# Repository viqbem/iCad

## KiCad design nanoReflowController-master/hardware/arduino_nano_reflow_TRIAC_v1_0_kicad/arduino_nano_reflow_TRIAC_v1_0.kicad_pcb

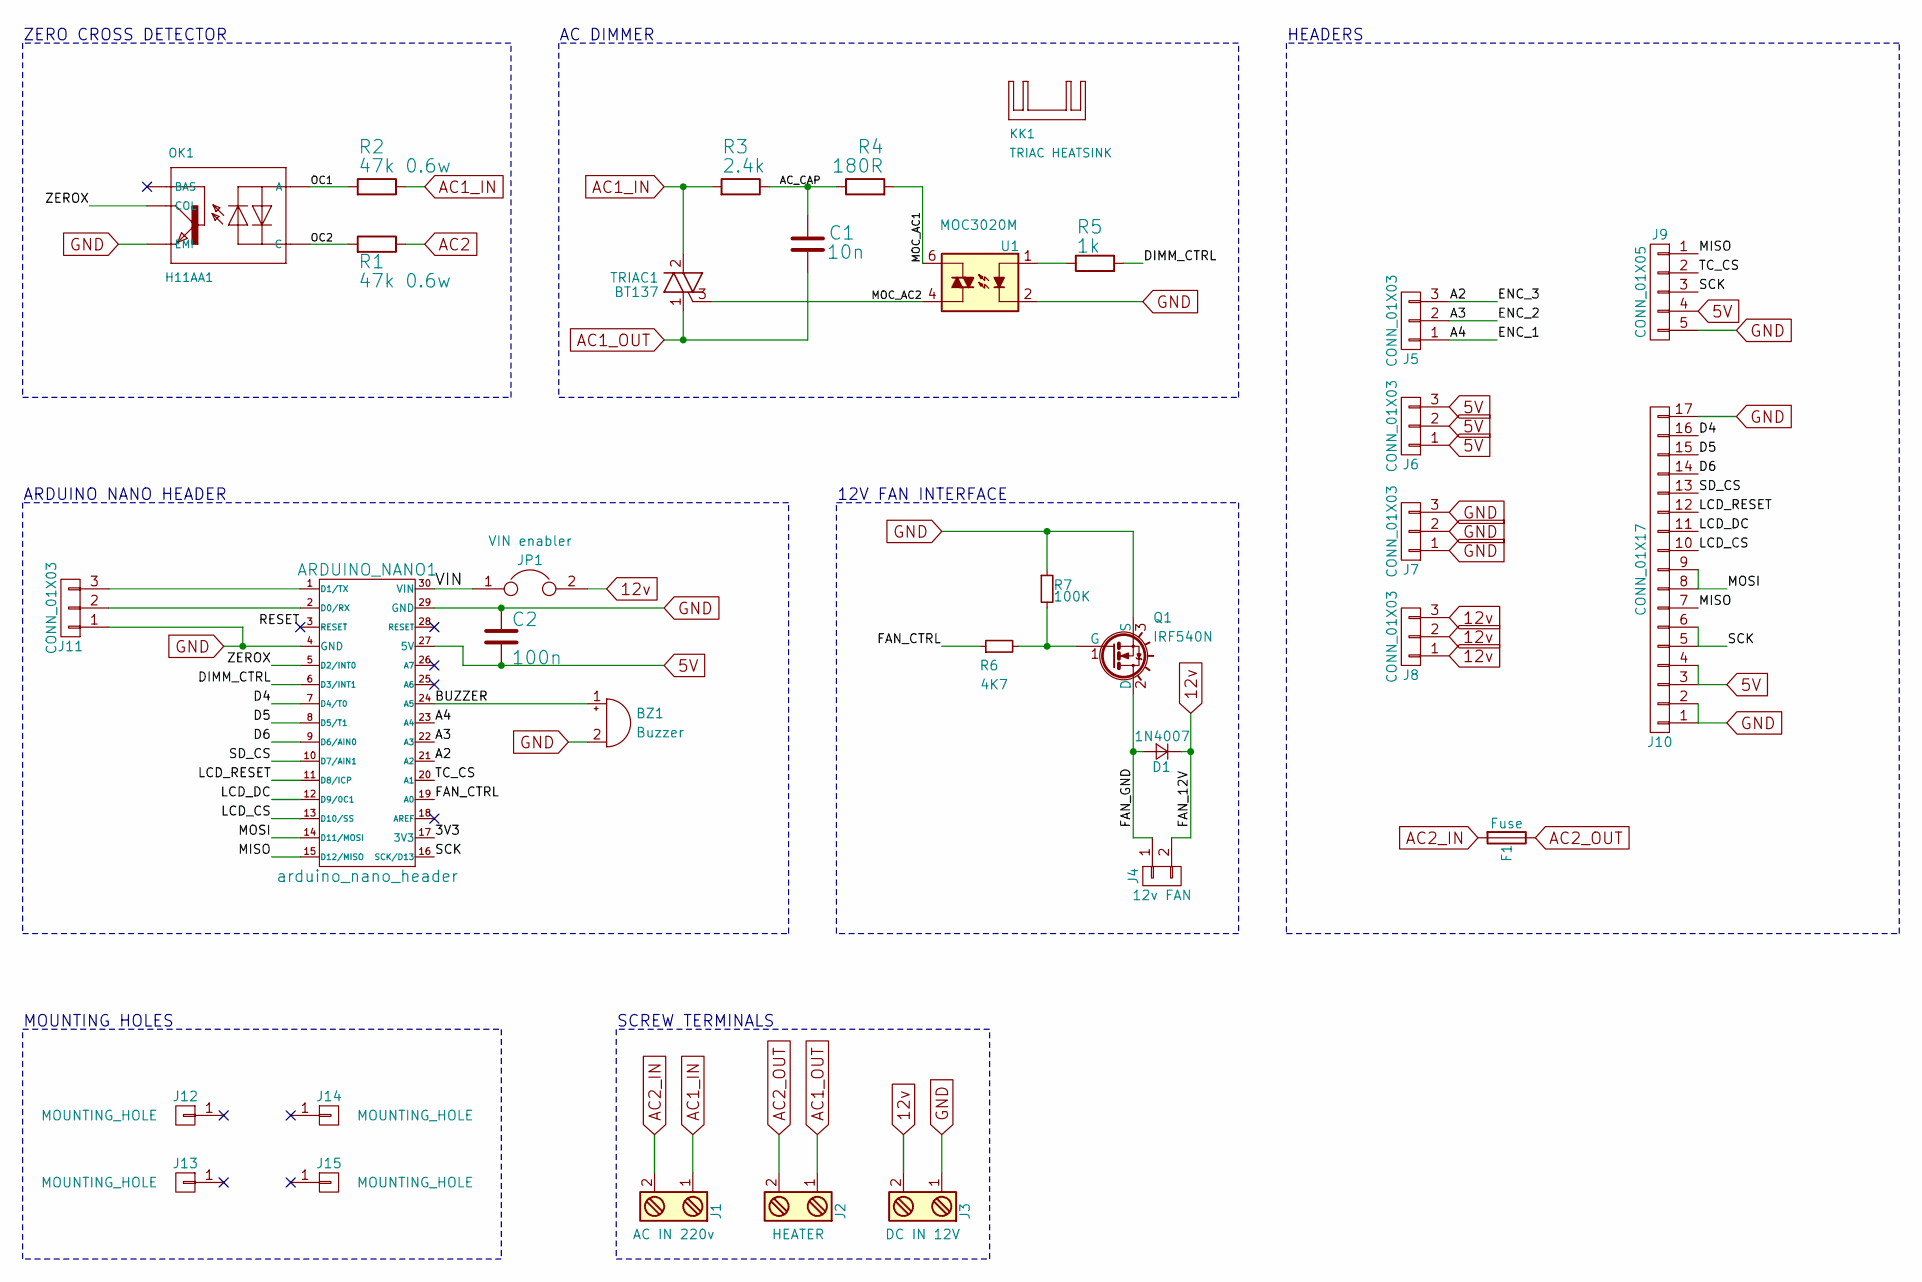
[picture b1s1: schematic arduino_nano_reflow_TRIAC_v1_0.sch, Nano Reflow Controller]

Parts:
ARDUINO_NANO1: arduino_nano_header
BZ1: Buzzer; Buzzer_12x9.5RM7.6
C1: 10n; C_Disc_D4.3mm_W1.9mm_P5.00mm
C2: 100n; C_1206_HandSoldering
D1: 1N4007; D_A-405_P5.08mm_Vertical_AnodeUp
F1: Fuse; Fuseholder5x20_horiz_open_inline_Type-I
J1: AC IN 220v; TerminalBlock_Pheonix_MKDS1.5-2pol
J2: HEATER; TerminalBlock_Pheonix_MKDS1.5-2pol
J3: DC IN 12V; TerminalBlock_Pheonix_MKDS1.5-2pol
J4: 12v FAN; Pin_Header_Straight_2x01_Pitch2.54mm
J5, J6, J7, J8, J11: CONN_01X03; Pin_Header_Straight_1x03_Pitch2.54mm
J9: CONN_01X05; Pin_Header_Straight_1x05_Pitch2.54mm
J10: CONN_01X17; Pin_Header_Straight_1x17_Pitch2.54mm
J12, J13, J14, J15: MOUNTING_HOLE; MountingHole_3.2mm_M3_Pad_Via
JP1: VIN enabler; Pin_Header_Straight_1x02_Pitch2.54mm
KK1: TRIAC HEATSINK; SK_09_20_SA_TO_220
OK1: H11AA1; DIP-6_W7.62mm_LongPads
Q1: IRF540N; TO-220_Vertical
R1, R2: 47k 0.6w; R_Axial_DIN0207_L6.3mm_D2.5mm_P7.62mm_Horizontal
R3: 2.4k; R_Axial_DIN0207_L6.3mm_D2.5mm_P7.62mm_Horizontal
R4: 180R; R_Axial_DIN0207_L6.3mm_D2.5mm_P7.62mm_Horizontal
R5: 1k; R_Axial_DIN0207_L6.3mm_D2.5mm_P7.62mm_Horizontal
R6: 4K7; R_Axial_DIN0309_L9.0mm_D3.2mm_P12.70mm_Horizontal
R7: 100K; R_1206_HandSoldering
TRIAC1: BT137; TO-220_Vertical_BT137
U1: MOC3020M; DIP-6_W7.62mm_LongPads

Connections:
5V: ARDUINO_NANO1.27 (5V), C2.2, J6.1, J6.2, J6.3, J9.4, J10.3, J10.4
12v: D1.1 (K), J3.2, J4.2, J8.1, J8.2, J8.3, JP1.2
/3V3: ARDUINO_NANO1.17 (3V3)
/A2: ARDUINO_NANO1.21 (A2), J5.3
/A3: ARDUINO_NANO1.22 (A3), J5.2
/A4: ARDUINO_NANO1.23 (A4), J5.1
/AC_CAP: C1.2, R3.1, R4.1
/BUZZER: ARDUINO_NANO1.24 (A5), BZ1.1 (-)
/D4: ARDUINO_NANO1.7 (D4/T0), J10.16
/D5: ARDUINO_NANO1.8 (D5/T1), J10.15
/D6: ARDUINO_NANO1.9 (D6/AIN0), J10.14
/DIMM_CTRL: ARDUINO_NANO1.6 (D3/INT1), R5.2
/FAN_CTRL: ARDUINO_NANO1.19 (A0), R6.1
/FAN_GND: D1.2 (A), J4.1, Q1.2 (D)
/LCD_CS: ARDUINO_NANO1.13 (D10/SS), J10.10
/LCD_DC: ARDUINO_NANO1.12 (D9/0C1), J10.11
/LCD_RESET: ARDUINO_NANO1.11 (D8/ICP), J10.12
/MISO: ARDUINO_NANO1.15 (D12/MISO), J9.1, J10.7
/MOC_AC1: R4.2, U1.6
/MOC_AC2: TRIAC1.3 (G), U1.4
/MOSI: ARDUINO_NANO1.14 (D11/MOSI), J10.8, J10.9
/OC1: OK1.1 (A), R2.2
/OC2: OK1.2 (C), R1.2
/RESET: ARDUINO_NANO1.3 (RESET)
/SCK: ARDUINO_NANO1.16 (SCK/D13), J9.3, J10.5, J10.6
/SD_CS: ARDUINO_NANO1.10 (D7/AIN1), J10.13
/TC_CS: ARDUINO_NANO1.20 (A1), J9.2
/VIN: ARDUINO_NANO1.30 (VIN), JP1.1
/ZEROX: ARDUINO_NANO1.5 (D2/INT0), OK1.5 (COL)
AC1_IN: J1.1, R2.1, R3.2, TRIAC1.2 (A2)
AC1_OUT: C1.1, J2.1, TRIAC1.1 (A1)
AC2: R1.1
AC2_IN: F1.2, J1.2
AC2_OUT: F1.1, J2.2
GND: ARDUINO_NANO1.4 (GND), ARDUINO_NANO1.29 (GND), BZ1.2 (+), C2.1, J3.1, J7.1, J7.2, J7.3, J9.5, J10.1, J10.2, J10.17, J11.1, OK1.4 (EMI), Q1.3 (S), R7.1, U1.2
unnamed: ARDUINO_NANO1.1 (D1/TX), J11.3
unnamed: ARDUINO_NANO1.2 (D0/RX), J11.2
unnamed: Q1.1 (G), R6.2, R7.2
unnamed: R5.1, U1.1

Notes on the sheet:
ZERO CROSS DETECTOR
AC DIMMER
12V FAN INTERFACE
HEADERS
ARDUINO NANO HEADER
SCREW TERMINALS
MOUNTING HOLES

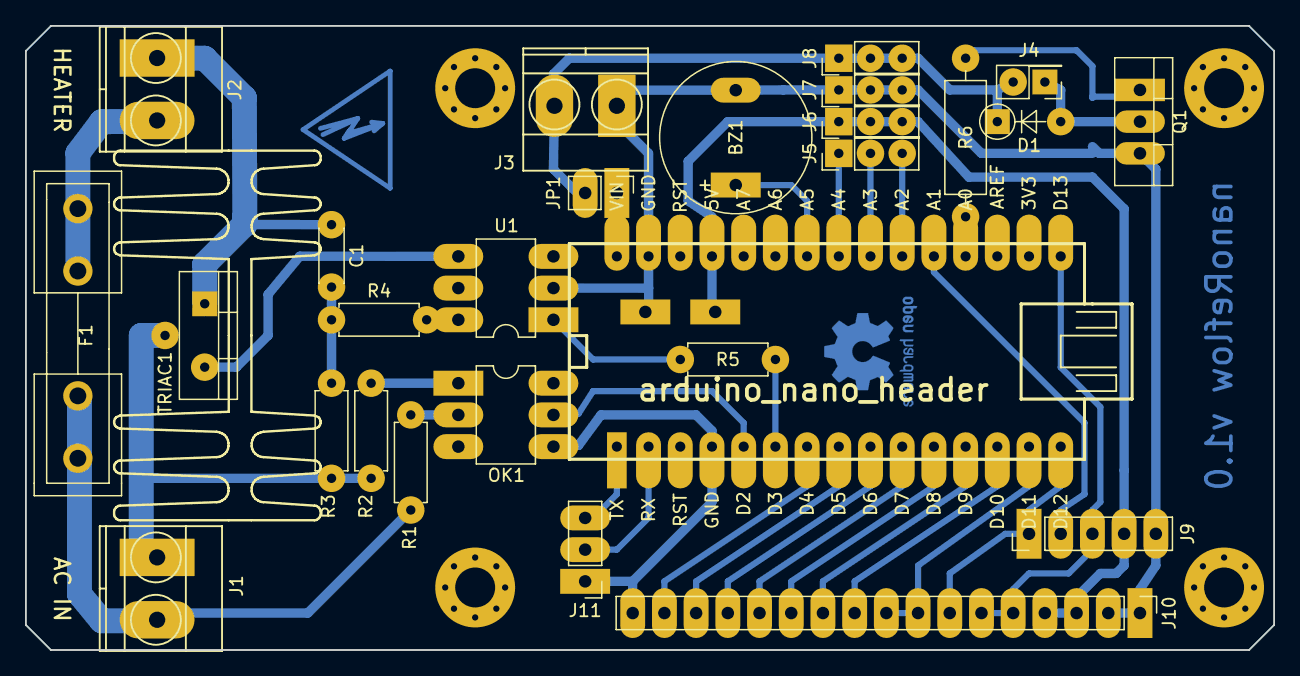
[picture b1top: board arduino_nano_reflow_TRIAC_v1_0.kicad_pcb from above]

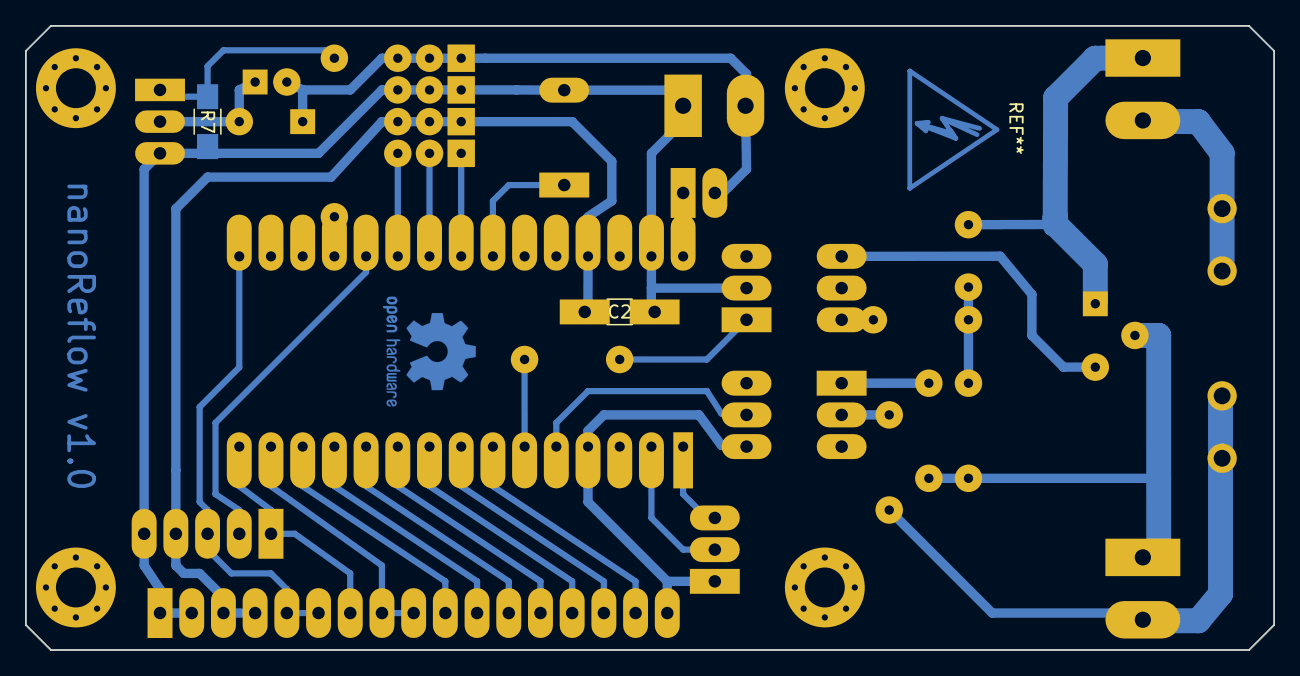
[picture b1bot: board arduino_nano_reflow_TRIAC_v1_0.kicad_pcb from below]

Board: 2 copper layers, 100.0 x 50.0 mm, 34 parts (2 on the bottom side), 36 nets.

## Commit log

2015-08-10 Create Calibrador
2015-08-10 archivos Eagle
2015-08-11 Hembrilla seguridad HBS
2015-08-13 Goma pasacables
2016-05-15 elimino archivos innecesarios
2016-05-15 Protection for outdoor wireless doorbell
2016-06-19 i add parts list
2016-06-19 I add exploded assembly
2016-08-28 I add proposed projec
2016-09-04 agrego archivos
2016-09-04 Dispositivo RGB para K8200
2016-09-10 manufacturing files
2017-04-01 Accesorio domo
2017-04-01 elimino archivos
2017-04-01 Electric connect
2017-04-08 actualización
2017-04-17 modifico archivos
2017-04-29 añado x2 carpetas nuevas
2017-04-29 Thermostat XH-W1411
2017-04-29 agrego archivos nuevos
2017-08-25 agrego carpeta
2017-08-28 arreglos
2017-08-28 elimino archivor innecesarios
2017-10-16 archivos modificados
2017-10-17 agrego archivos .nc
2018-11-25 Add files via upload
    Agrego imagen
2019-09-12 kit de reloj
2019-09-12 Sistema iluminación eco
